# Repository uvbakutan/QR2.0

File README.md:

# QR2.0
Arudino Pro Micro Quad-Copter;

Parts Used:

  - Arduino pro micro 5V ( leonardo )
  - GY_80 10DOF IMU
  - JY-MCU HC-06 V1.03 bluetooth module
  - 4.2V 46500RPM magnetic coreless motor for RC helicopter
  - 7.4V 350mAh lipo battery

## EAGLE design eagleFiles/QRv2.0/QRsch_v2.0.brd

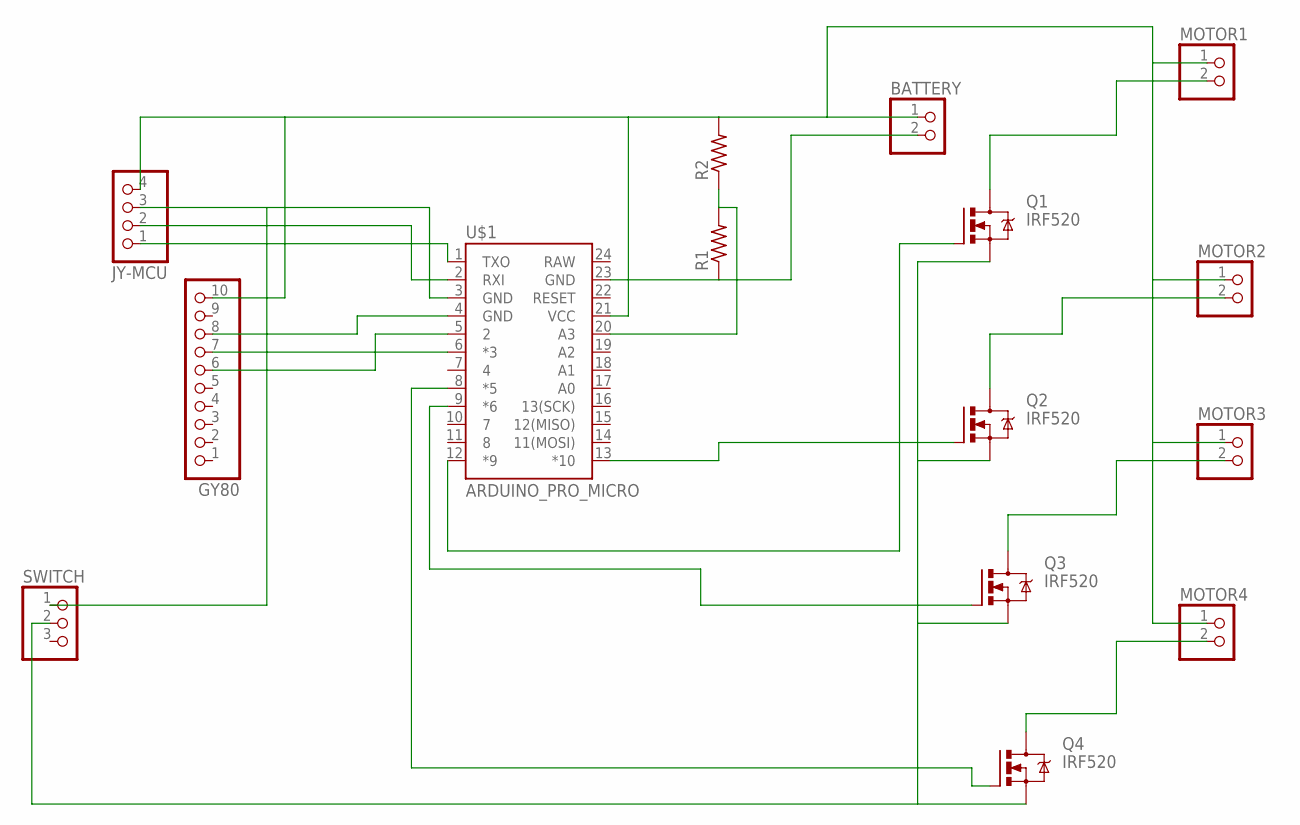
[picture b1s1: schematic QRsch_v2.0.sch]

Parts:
BATTERY: PINHD-1X2/90; 1X02/90
GY80: PINHD-1X10; 1X10
JY-MCU: PINHD-1X4; 1X04
MOTOR1, MOTOR2, MOTOR3, MOTOR4: PINHD-1X2/90; 1X02/90
Q1, Q2, Q3, Q4: IRF520; TO220BV
R1, R2: R-US_0207/7; 0207/7
SWITCH: PINHD-1X3; 1X03
U$1: ARDUINO_PRO_MICRO

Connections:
GND: BATTERY.2, GY80.8, JY-MCU.3, R1.1, SWITCH.1, U$1.3 (GND), U$1.4 (GND), U$1.23 (GND)
unnamed: R1.2, R2.1, U$1.20 (A3)
unnamed: Q4.G, U$1.8 (*5)
unnamed: Q3.G, U$1.9 (*6)
unnamed: Q1.G, U$1.12 (*9)
unnamed: MOTOR1.2, Q1.D
unnamed: JY-MCU.2, U$1.2 (RXI)
unnamed: JY-MCU.1, U$1.1 (TXO)
unnamed: GY80.7, U$1.6 (*3)
unnamed: GY80.6, U$1.5 (2)
unnamed: MOTOR2.2, Q2.D
unnamed: MOTOR3.2, Q3.D
unnamed: MOTOR4.2, Q4.D
unnamed: Q1.S, Q2.S, Q3.S, Q4.S, SWITCH.2
unnamed: Q2.G, U$1.13 (*10)
RAW: BATTERY.1, GY80.10, JY-MCU.4, MOTOR1.1, MOTOR2.1, MOTOR3.1, MOTOR4.1, R2.2, U$1.21 (VCC)

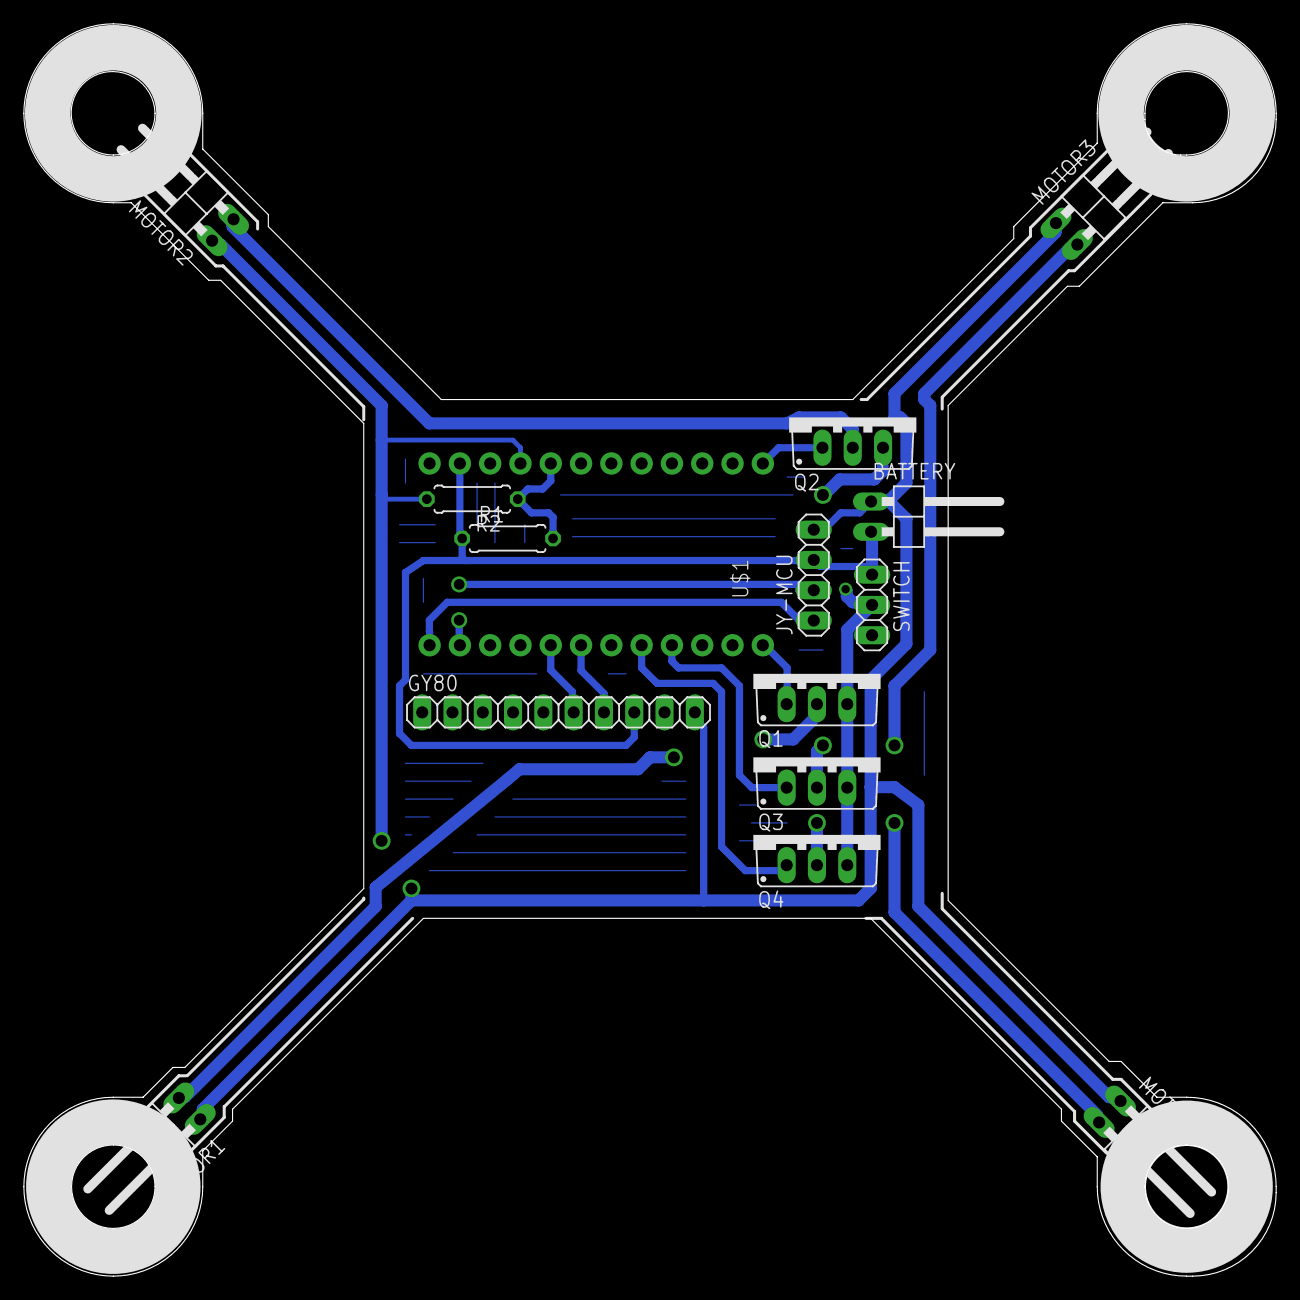
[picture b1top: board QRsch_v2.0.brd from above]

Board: 2 copper layers, 105.0 x 105.0 mm, 15 parts (0 on the bottom side), 16 nets.

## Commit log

2015-02-28 added eagle files
2015-03-01 created sliders in processing
2015-03-01 changed the slider appereance
2015-03-01 arduino program that sends Orientation, and recieves Motor speed
2015-03-03 implemented simple communication protocol between arduino and processing
2015-03-03 added 3Dcube for angle representation, implemented communication
2015-03-04 added pid regulation and separated the communication part
2015-03-04 added slider for rotation and angle coeficient, changed the layout
2015-03-21 added arduino libreries
2015-03-21 changed slider class you can make it return to first position, added sliders for tunning
2015-03-21 changed pid ranges, variable names and code clean up
2015-03-22 added processing code for Android controller, implemented joystick
2015-03-22 changed folder name
2015-03-23 added bluetooth communication
2015-03-23 separated tuning and controller arduino sketch
2015-03-23 added arduino sketch for android controller
2015-03-23 added button for discovery of bluetooth devices
2015-03-23 fixed the pid coefficients, changed the message for sending
2015-03-25 added Yaw compensation, and increased the joystich desired angles
2015-03-25 added battery indicator, now by pressing C agian you disconnect, not displaying the whole message from arduino only taking battery
2015-04-17 added yaw control
2015-05-29 made new PCB design
2015-05-29 added solidWorks and stl model of the motor holder

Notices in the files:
parts and their libraries:
SparkFun-Boards: Licensing: Creative Commons ShareAlike 4.0 International - https://creativecommons.org/licenses/by-sa/4.0
